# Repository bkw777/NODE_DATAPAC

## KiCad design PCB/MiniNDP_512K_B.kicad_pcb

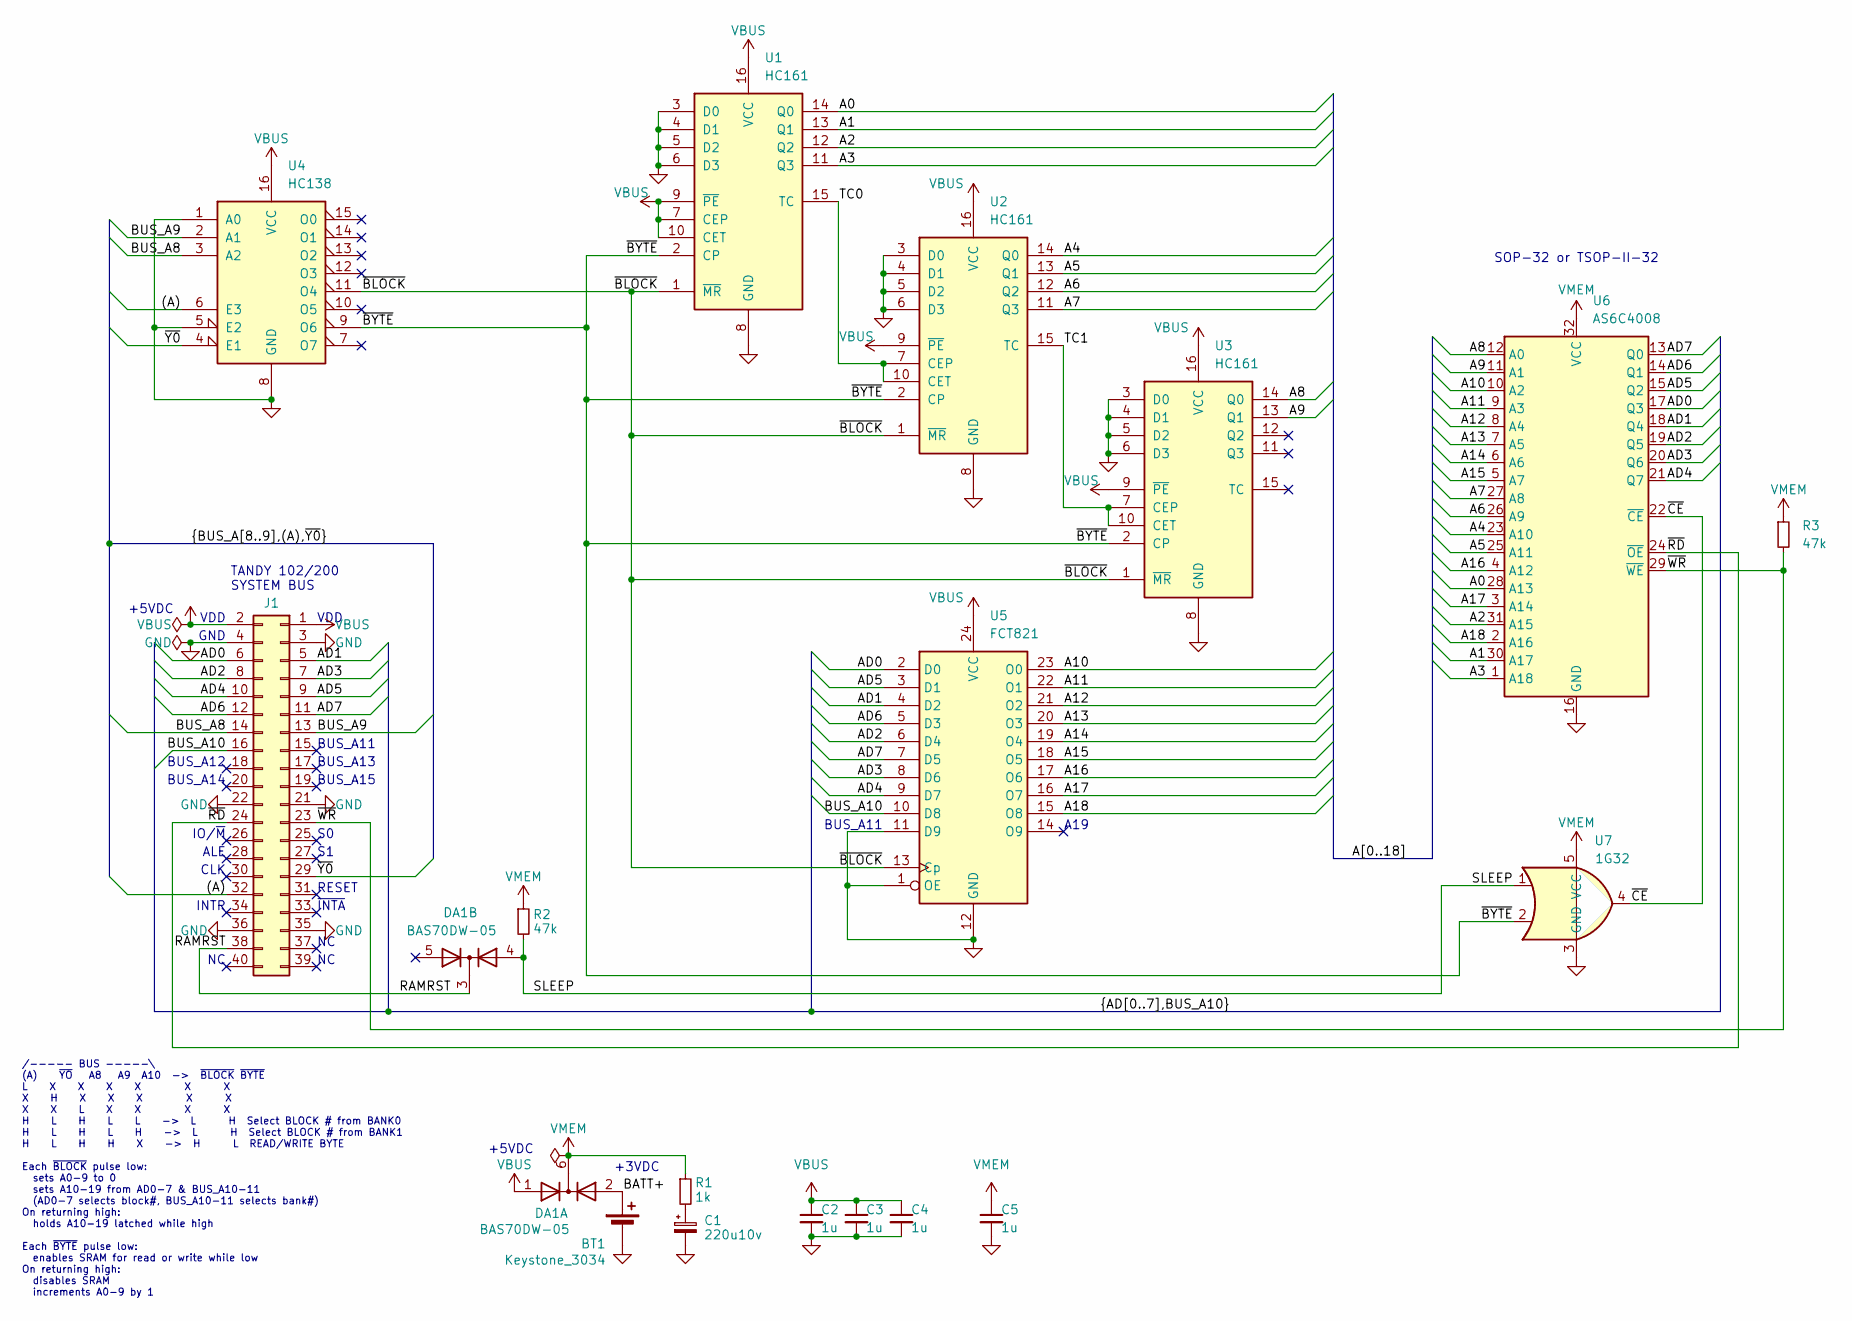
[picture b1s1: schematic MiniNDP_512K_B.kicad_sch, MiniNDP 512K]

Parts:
BT1: Keystone_3034; Keystone_3028_3034
C1: 220u10v; CP_6032
C2, C3, C4, C5: 1u; C_0805
DA1: BAS70DW-05; SOT-363_SC-70-6_symmetric
J1: Conn_02x20_Odd_Even; IDC-Header_2x20_P2.54mm_Vertical
R1: 1k; R_0805
R2, R3: 47k; R_0805
U1, U2, U3: HC161; TSSOP-16
U4: HC138; TSSOP-16
U5: FCT821; SOIC-24
U6: AS6C4008; TSOP-II-SOP-32_dual
U7: 1G32; SOT-353_SC-70-5

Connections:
/(A): J1.32, U4.6 (E3)
/A0: U1.14 (Q0), U6.28 (A13)
/A1: U1.13 (Q1), U6.30 (A17)
/A2: U1.12 (Q2), U6.31 (A15)
/A3: U1.11 (Q3), U6.1 (A18)
/A4: U2.14 (Q0), U6.23 (A10)
/A5: U2.13 (Q1), U6.25 (A11)
/A6: U2.12 (Q2), U6.26 (A9)
/A7: U2.11 (Q3), U6.27 (A8)
/A8: U3.14 (Q0), U6.12 (A0)
/A9: U3.13 (Q1), U6.11 (A1)
/A10: U5.23 (O0), U6.10 (A2)
/A11: U5.22 (O1), U6.9 (A3)
/A12: U5.21 (O2), U6.8 (A4)
/A13: U5.20 (O3), U6.7 (A5)
/A14: U5.19 (O4), U6.6 (A6)
/A15: U5.18 (O5), U6.5 (A7)
/A16: U5.17 (O6), U6.4 (A12)
/A17: U5.16 (O7), U6.3 (A14)
/A18: U5.15 (O8), U6.2 (A16)
/AD0: J1.6, U5.2 (D0), U6.17 (Q3)
/AD1: J1.5, U5.4 (D2), U6.18 (Q4)
/AD2: J1.8, U5.6 (D4), U6.19 (Q5)
/AD3: J1.7, U5.8 (D6), U6.20 (Q6)
/AD4: J1.10, U5.9 (D7), U6.21 (Q7)
/AD5: J1.9, U5.3 (D1), U6.15 (Q2)
/AD6: J1.12, U5.5 (D3), U6.14 (Q1)
/AD7: J1.11, U5.7 (D5), U6.13 (Q0)
/BATT+: BT1.1 (+), DA1.2 (A)
/BUS_A8: J1.14, U4.3 (A2)
/BUS_A9: J1.13, U4.2 (A1)
/BUS_A10: J1.16, U5.10 (D8)
/RAMRST: DA1.3 (K), J1.38
/SLEEP: DA1.4 (A), R2.2, U7.1
/TC0: U1.15 (TC), U2.7 (CEP), U2.10 (CET)
/TC1: U2.15 (TC), U3.7 (CEP), U3.10 (CET)
/~BLOCK: U1.1 (~MR), U2.1 (~MR), U3.1 (~MR), U4.11 (O4), U5.13 (Cp)
/~BYTE: U1.2 (CP), U2.2 (CP), U3.2 (CP), U4.9 (O6), U7.2
/~CE: U6.22 (~CE), U7.4
/~RD: J1.24, U6.24 (~OE)
/~WR: J1.23, R3.2, U6.29 (~WE)
/~Y0: J1.29, U4.4 (E1)
GND: BT1.2 (-), C1.2, C2.2, C3.2, C4.2, C5.2, J1.3, J1.4, J1.21, J1.22, J1.35, J1.36, U1.3 (D0), U1.4 (D1), U1.5 (D2), U1.6 (D3), U1.8 (GND), U2.3 (D0), U2.4 (D1), U2.5 (D2), U2.6 (D3), U2.8 (GND), U3.3 (D0), U3.4 (D1), U3.5 (D2), U3.6 (D3), U3.8 (GND), U4.1 (A0), U4.5 (E2), U4.8 (GND), U5.1 (OE), U5.11 (D9), U5.12 (GND), U6.16 (GND), U7.3 (GND)
unnamed: C1.1, R1.2
VBUS: C2.1, C3.1, C4.1, DA1.1 (A), J1.1, J1.2, U1.7 (CEP), U1.9 (~PE), U1.10 (CET), U1.16 (VCC), U2.9 (~PE), U2.16 (VCC), U3.9 (~PE), U3.16 (VCC), U4.16 (VCC), U5.24 (VCC)
VMEM: C5.1, DA1.6 (K), R1.1, R2.1, R3.1, U6.32 (VCC), U7.5 (VCC)

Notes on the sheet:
BUS_A11
TANDY 102/200 SYSTEM BUS
+5VDC
BUS_A15
INTR
BUS_A14
ALE
SOP-32 or TSOP-II-32
~{INTA}
CLK
GND
IO/~{M}
VDD
/----- BUS -----\ (A) ~{YO} A8 A9 A10 -> ~{BLOCK} ~{BYTE} L X X X X X X X H X X X X X X X L X X X X H L H L L -> L H Select BLOCK # from BANK0 H L H L H -> L H Select BLOCK # from BANK1 H L H H X -> H L READ/WRITE BYTE Each ~{BLOCK} pulse low: sets A0-9 to 0 sets A10-19 from AD0-7 & BUS_A10-11 (AD0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
+3VDC
RESET
A19
BUS_A13
BUS_A12

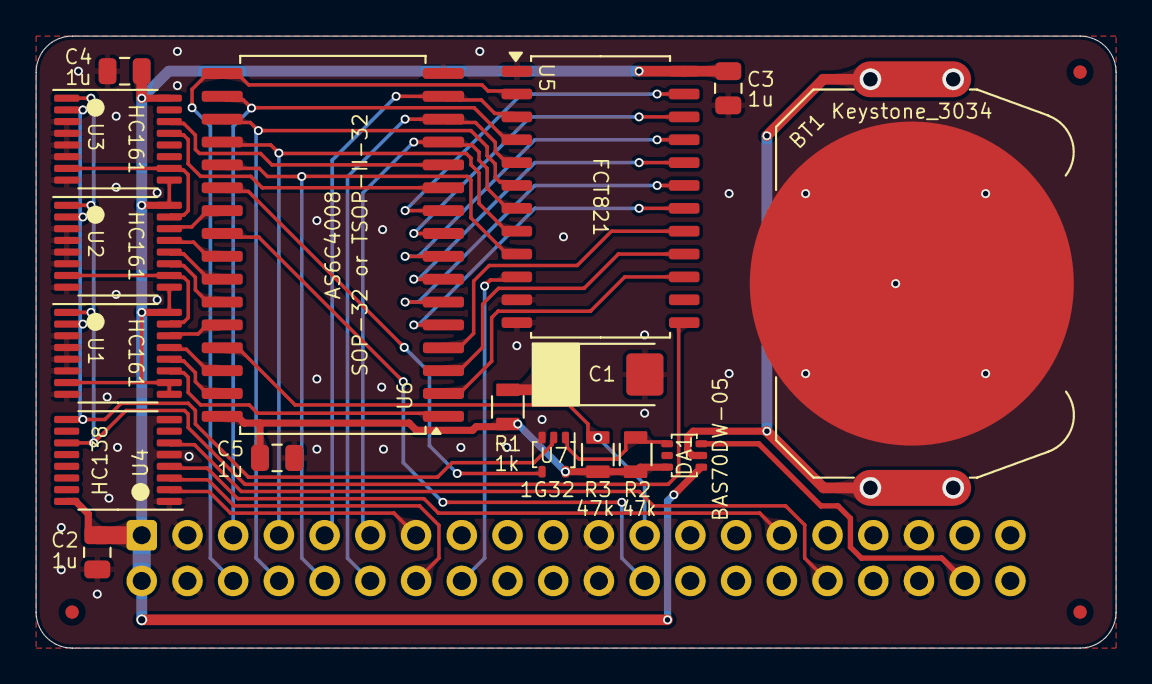
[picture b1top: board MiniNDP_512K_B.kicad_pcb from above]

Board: 2 copper layers, 60.0 x 34.0 mm, 22 parts (1 on the bottom side), 46 nets.

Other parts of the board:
ENCLOSURE: MiniNDP_Cover
F2, F2#2, F3: Fiducial_0.75_1.5

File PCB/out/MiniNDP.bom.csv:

"Reference","Value","Datasheet","Footprint","Qty","DNP","MPN","Description"
"BT1","Keystone_3034","datasheets/Keystone_3034.pdf","000_LOCAL:Keystone_3028_3034","1","","Keystone 3034","SMT 20mm x 3.2mm coin cell holder"
"C1","220u10v","datasheets/TAJ.odf","000_LOCAL:CP_6032","1","","TAJC227K010RNJ","CAP TANT 220UF 10% 10V 2312"
"C2,C3,C4,C5","1u","datasheets/CL21B105KAFNNNE.pdf","000_LOCAL:C_0805","4","","CL21B105KAFNNNE","CAP CER 1UF 25V X7R 0805"
"DA1","BAS70DW-05","datasheets/BAS70.pdf","000_LOCAL:SOT-363_SC-70-6_symmetric","1","","BAS70DW-05-7-F","DIODE ARR SCHOTT 70V 70MA SOT363 2-PAIR COMMON-CATHODE"
"J1","Conn_02x20_Odd_Even","datasheets/2x20_male_boxed.pdf","000_LOCAL:IDC-Header_2x20_P2.54mm_Vertical","1","","302-S401","CONN HEADER VERT 40POS 2.54MM"
"R1","1k","datasheets/RK73.pdf","000_LOCAL:R_0805","1","","RK73B2ATTD102J","RES 1K OHM 5% 1/4W 0805"
"R2,R3","47k","datasheets/sei-rmcf_rmcp.pdf","000_LOCAL:R_0805","2","","RMCF0805FT47K0","RES 47K OHM 1% 1/8W 0805"
"U1,U2,U3","HC161","datasheets/HC161.pdf","000_LOCAL:TSSOP-16","3","","74HC161PW,118","IC BINARY COUNTER 4-BIT 16TSSOP"
"U4","HC138","datasheets/HC138.pdf","000_LOCAL:TSSOP-16","1","","74HC138PW,118","IC DECODER/DEMUX 1X3:8 16TSSOP"
"U5","HC574","datasheets/HC574.pdf","000_LOCAL:TSSOP-20","1","","74HC574PW,118","IC FF D-TYPE SNGL 8BIT 20TSSOP"
"U6","AS6C4008","datasheets/AS6C4008.pdf","000_LOCAL:TSOP32-dual","1","","AS6C4008-55STIN","IC SRAM 512Kx8 PARALLEL STSOP-32"
"U7","1G32","datasheets/LVC1G32.pdf","000_LOCAL:SOT-353_SC-70-5","1","","74LVC1G32GW,125","IC GATE OR 1CH 2-INP 5TSSOP"
"U8","1G79","datasheets/LVC1G79.pdf","000_LOCAL:SOT-353_SC-70-5","1","","74LVC1G79GW,125","IC FF D-TYPE SNGL 1BIT 5TSSOP"

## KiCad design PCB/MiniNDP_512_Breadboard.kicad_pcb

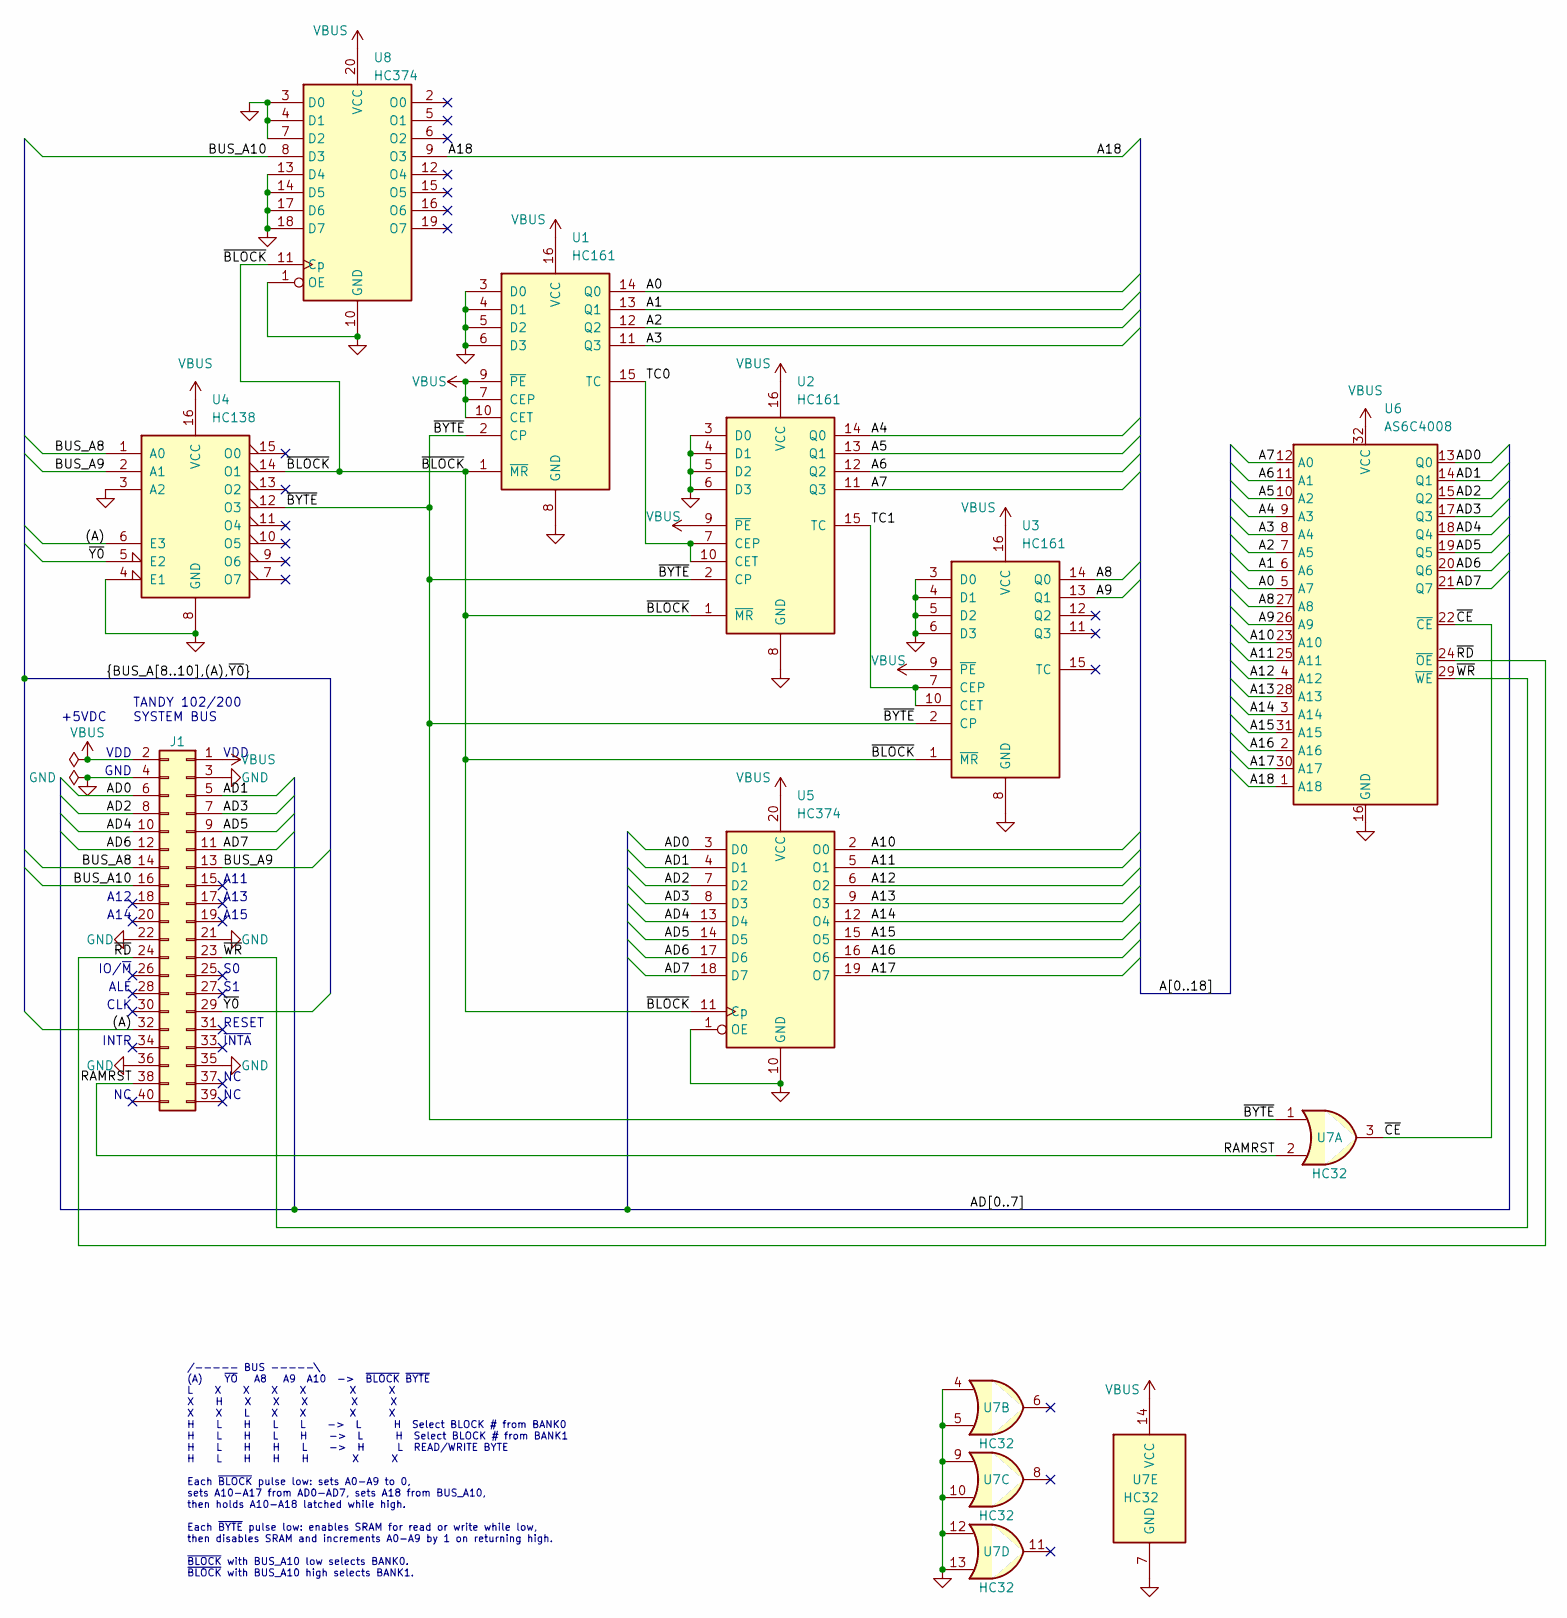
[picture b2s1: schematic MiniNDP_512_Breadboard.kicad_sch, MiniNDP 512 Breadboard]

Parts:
J1: Conn_02x20_Odd_Even; IDC-Header_2x20_P2.54mm_Vertical
U1, U2, U3: HC161; DIP-16_W7.62mm
U4: HC138; DIP-16_W7.62mm
U5, U8: HC374; DIP-20_W7.62mm
U6: AS6C4008; DIP-32_W15.24mm
U7: HC32; DIP-14_W7.62mm

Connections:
/(A): J1.32, U4.6 (E3)
/A0: U1.14 (Q0), U6.5 (A7)
/A1: U1.13 (Q1), U6.6 (A6)
/A2: U1.12 (Q2), U6.7 (A5)
/A3: U1.11 (Q3), U6.8 (A4)
/A4: U2.14 (Q0), U6.9 (A3)
/A5: U2.13 (Q1), U6.10 (A2)
/A6: U2.12 (Q2), U6.11 (A1)
/A7: U2.11 (Q3), U6.12 (A0)
/A8: U3.14 (Q0), U6.27 (A8)
/A9: U3.13 (Q1), U6.26 (A9)
/A10: U5.2 (O0), U6.23 (A10)
/A11: U5.5 (O1), U6.25 (A11)
/A12: U5.6 (O2), U6.4 (A12)
/A13: U5.9 (O3), U6.28 (A13)
/A14: U5.12 (O4), U6.3 (A14)
/A15: U5.15 (O5), U6.31 (A15)
/A16: U5.16 (O6), U6.2 (A16)
/A17: U5.19 (O7), U6.30 (A17)
/A18: U6.1 (A18), U8.9 (O3)
/AD0: J1.6, U5.3 (D0), U6.13 (Q0)
/AD1: J1.5, U5.4 (D1), U6.14 (Q1)
/AD2: J1.8, U5.7 (D2), U6.15 (Q2)
/AD3: J1.7, U5.8 (D3), U6.17 (Q3)
/AD4: J1.10, U5.13 (D4), U6.18 (Q4)
/AD5: J1.9, U5.14 (D5), U6.19 (Q5)
/AD6: J1.12, U5.17 (D6), U6.20 (Q6)
/AD7: J1.11, U5.18 (D7), U6.21 (Q7)
/BUS_A8: J1.14, U4.1 (A0)
/BUS_A9: J1.13, U4.2 (A1)
/BUS_A10: J1.16, U8.8 (D3)
/RAMRST: J1.38, U7.2
/TC0: U1.15 (TC), U2.7 (CEP), U2.10 (CET)
/TC1: U2.15 (TC), U3.7 (CEP), U3.10 (CET)
/~BLOCK: U1.1 (~MR), U2.1 (~MR), U3.1 (~MR), U4.14 (O1), U5.11 (Cp), U8.11 (Cp)
/~BYTE: U1.2 (CP), U2.2 (CP), U3.2 (CP), U4.12 (O3), U7.1
/~CE: U6.22 (~CE), U7.3
/~RD: J1.24, U6.24 (~OE)
/~WR: J1.23, U6.29 (~WE)
/~Y0: J1.29, U4.5 (E2)
GND: J1.3, J1.4, J1.21, J1.22, J1.35, J1.36, U1.3 (D0), U1.4 (D1), U1.5 (D2), U1.6 (D3), U1.8 (GND), U2.3 (D0), U2.4 (D1), U2.5 (D2), U2.6 (D3), U2.8 (GND), U3.3 (D0), U3.4 (D1), U3.5 (D2), U3.6 (D3), U3.8 (GND), U4.3 (A2), U4.4 (E1), U4.8 (GND), U5.1 (OE), U5.10 (GND), U6.16 (GND), U7.4, U7.5, U7.7 (GND), U7.9, U7.10, U7.12, U7.13, U8.1 (OE), U8.3 (D0), U8.4 (D1), U8.7 (D2), U8.10 (GND), U8.13 (D4), U8.14 (D5), U8.17 (D6), U8.18 (D7)
VBUS: J1.1, J1.2, U1.7 (CEP), U1.9 (~PE), U1.10 (CET), U1.16 (VCC), U2.9 (~PE), U2.16 (VCC), U3.9 (~PE), U3.16 (VCC), U4.16 (VCC), U5.20 (VCC), U6.32 (VCC), U7.14 (VCC), U8.20 (VCC)

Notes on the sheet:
TANDY 102/200 SYSTEM BUS
+5VDC
A15
INTR
A14
ALE
~{INTA}
CLK
GND
/----- BUS -----\ (A) ~{YO} A8 A9 A10 -> ~{BLOCK} ~{BYTE} L X X X X X X X H X X X X X X X L X X X X H L H L L -> L H Select BLOCK # from BANK0 H L H L H -> L H Select BLOCK # from BANK1 H L H H L -> H L READ/WRITE BYTE H L H H H X X Each ~{BLOCK} pulse low: sets A0-A9 to 0, sets A10-A17 from AD0-AD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
IO/~{M}
VDD
RESET
A11
A13
A12

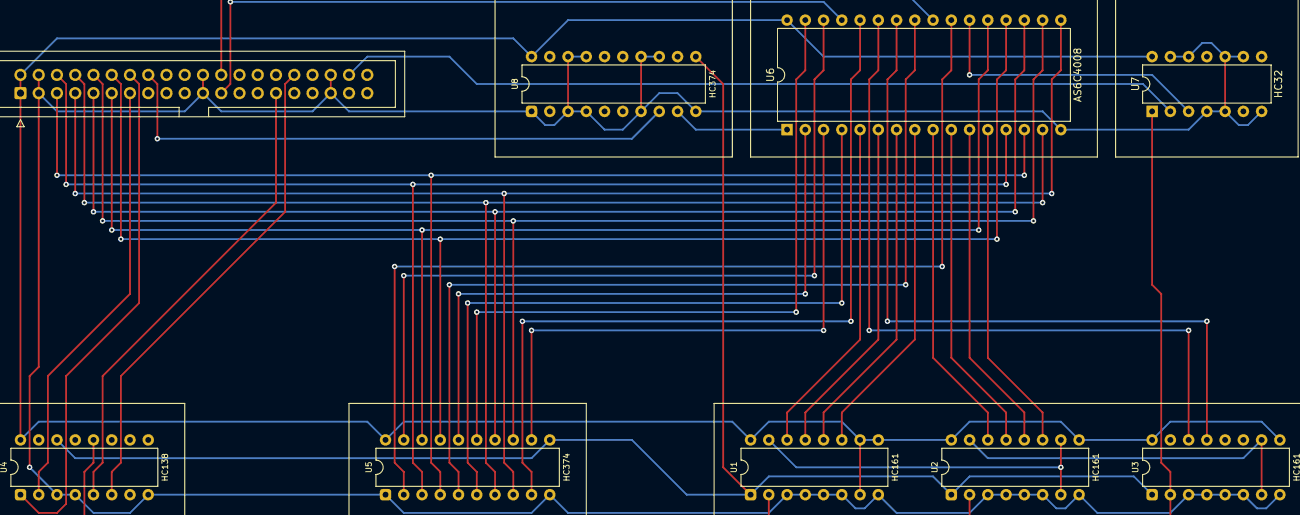
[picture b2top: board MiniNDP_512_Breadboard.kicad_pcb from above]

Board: 2 copper layers, 9 parts (0 on the bottom side), 42 nets.

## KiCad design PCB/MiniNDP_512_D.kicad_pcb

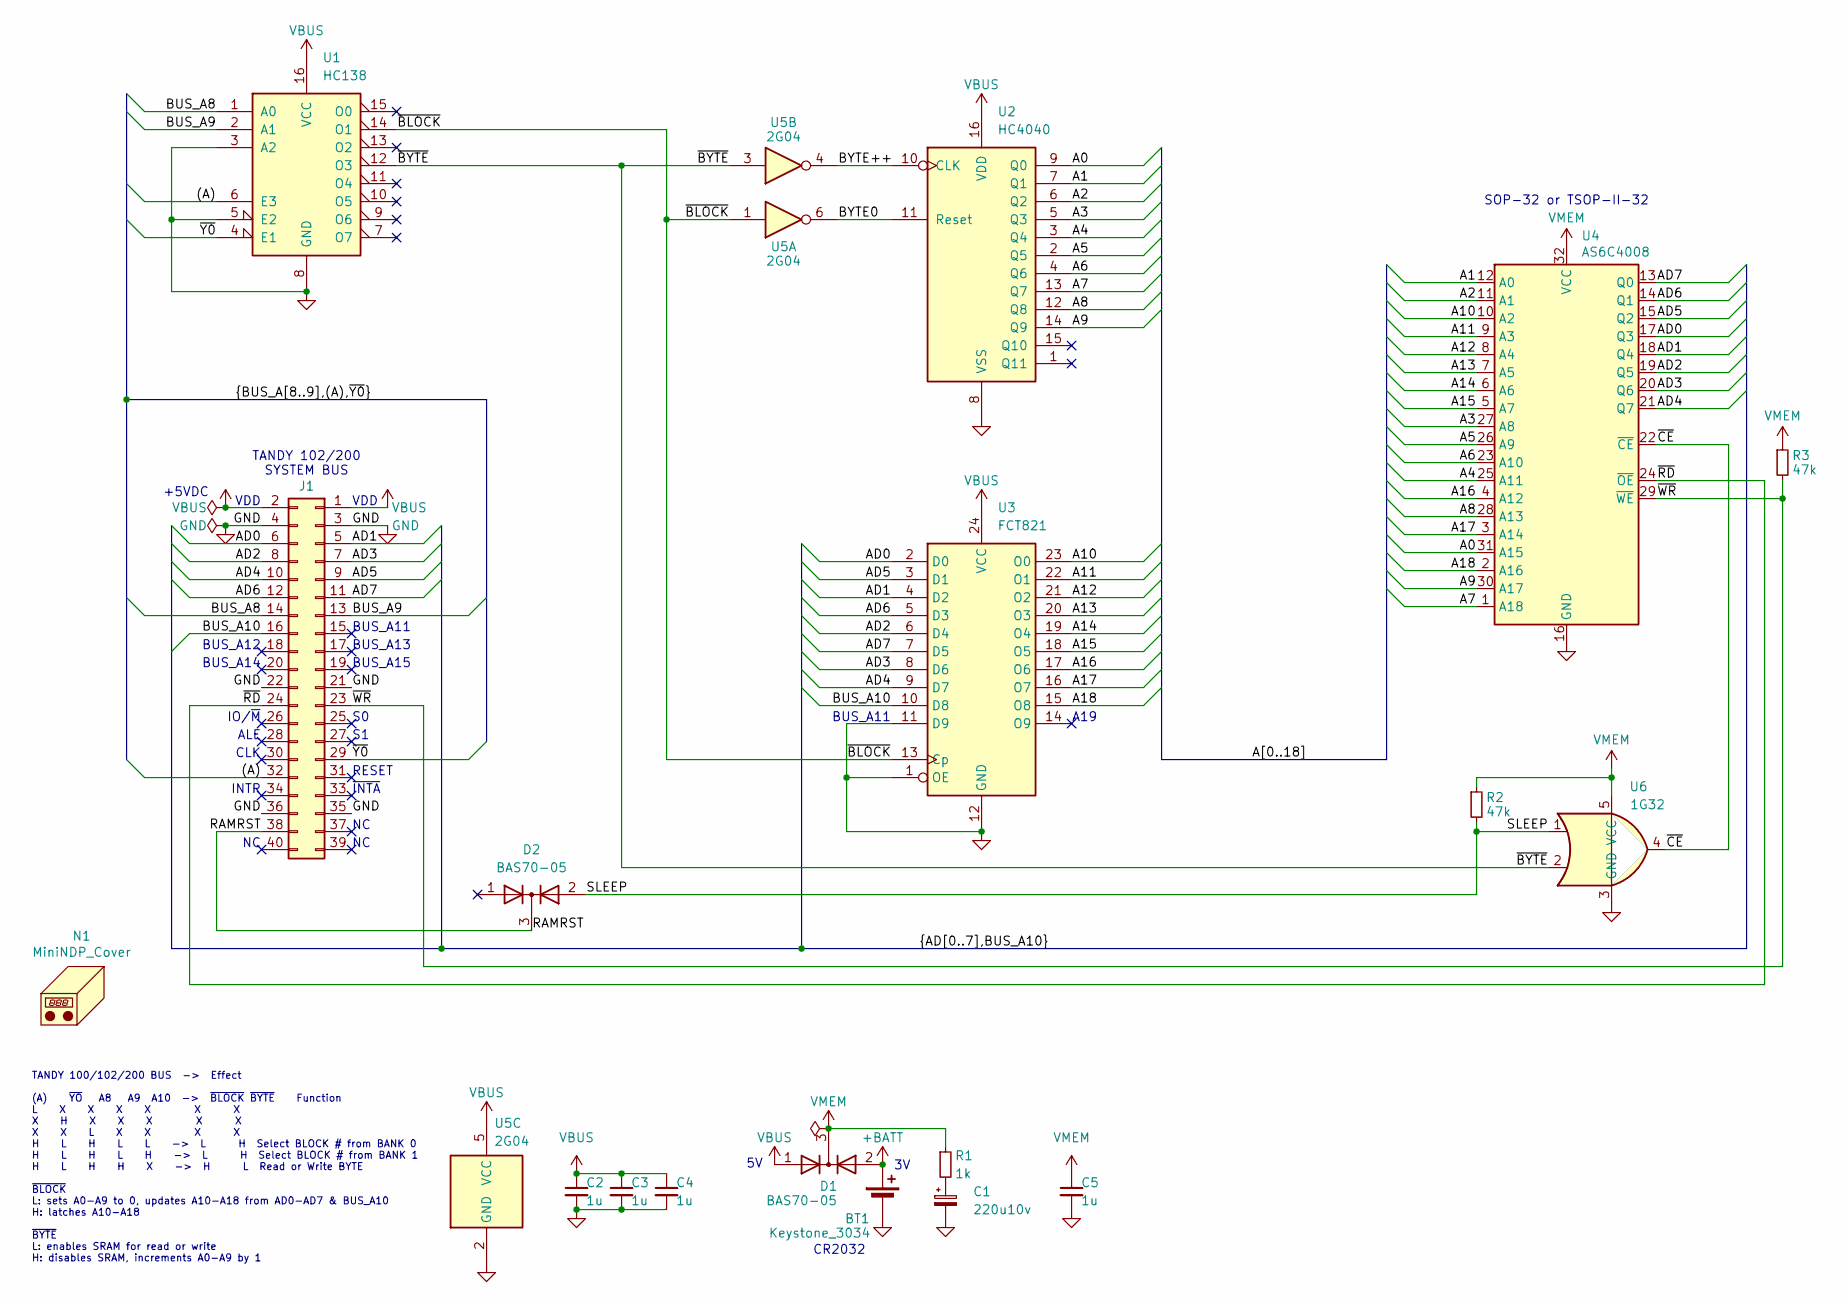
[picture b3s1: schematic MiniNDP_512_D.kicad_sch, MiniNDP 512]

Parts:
BT1: Keystone_3034; Keystone_3028_3034; MPN Keystone 3034
C1: 220u10v; CP_6032; MPN TAJC227K010RNJ
C2, C3, C4, C5: 1u; C_0805; MPN CL21B105KAFNNNE
D1, D2: BAS70-05; SOT-23; MPN BAS70-05-E3-08
J1: Conn_02x20_Odd_Even; IDC-Header_2x20_P2.54mm_Vertical; MPN 302-S401
N1: MiniNDP_Cover; MPN MiniNDP_Cover.stl
R1: 1k; R_0805; MPN RK73B2ATTD102J
R2, R3: 47k; R_0805; MPN RMCF0805FT47K0
U1: HC138; SOIC-16_3.9x9.9mm_P1.27mm; MPN 74AHC138D,118
U2: HC4040; SOIC-16_3.9x9.9mm_P1.27mm; MPN IC BINARY COUNTER 12-BIT 16SO
U3: FCT821; SOIC-24; MPN CY74FCT821BTSOC
U4: AS6C4008; TSOP-II-SOP-32_dual; MPN AS6C4008-55ZIN
U5: 2G04; TSOP-6_1.65x3.05mm_P0.95mm; MPN 74HC2G04GW,125
U6: 1G32; SOT-23-5; MPN SN74AHC1G32DBVR

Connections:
+BATT: BT1.1 (+), D1.2 (A)
/(A): J1.32, U1.6 (E3)
/A0: U2.9 (Q0), U4.31 (A15)
/A1: U2.7 (Q1), U4.12 (A0)
/A2: U2.6 (Q2), U4.11 (A1)
/A3: U2.5 (Q3), U4.27 (A8)
/A4: U2.3 (Q4), U4.25 (A11)
/A5: U2.2 (Q5), U4.26 (A9)
/A6: U2.4 (Q6), U4.23 (A10)
/A7: U2.13 (Q7), U4.1 (A18)
/A8: U2.12 (Q8), U4.28 (A13)
/A9: U2.14 (Q9), U4.30 (A17)
/A10: U3.23 (O0), U4.10 (A2)
/A11: U3.22 (O1), U4.9 (A3)
/A12: U3.21 (O2), U4.8 (A4)
/A13: U3.20 (O3), U4.7 (A5)
/A14: U3.19 (O4), U4.6 (A6)
/A15: U3.18 (O5), U4.5 (A7)
/A16: U3.17 (O6), U4.4 (A12)
/A17: U3.16 (O7), U4.3 (A14)
/A18: U3.15 (O8), U4.2 (A16)
/AD0: J1.6, U3.2 (D0), U4.17 (Q3)
/AD1: J1.5, U3.4 (D2), U4.18 (Q4)
/AD2: J1.8, U3.6 (D4), U4.19 (Q5)
/AD3: J1.7, U3.8 (D6), U4.20 (Q6)
/AD4: J1.10, U3.9 (D7), U4.21 (Q7)
/AD5: J1.9, U3.3 (D1), U4.15 (Q2)
/AD6: J1.12, U3.5 (D3), U4.14 (Q1)
/AD7: J1.11, U3.7 (D5), U4.13 (Q0)
/BUS_A8: J1.14, U1.1 (A0)
/BUS_A9: J1.13, U1.2 (A1)
/BUS_A10: J1.16, U3.10 (D8)
/BYTE0: U2.11 (Reset), U5.6
/BYTE++: U2.10 (CLK), U5.4
/RAMRST: D2.3 (K), J1.38
/SLEEP: D2.2 (A), R2.2, U6.1
/~BLOCK: U1.14 (O1), U3.13 (Cp), U5.1
/~BYTE: U1.12 (O3), U5.3, U6.2
/~CE: U4.22 (~CE), U6.4
/~RD: J1.24, U4.24 (~OE)
/~WR: J1.23, R3.2, U4.29 (~WE)
/~Y0: J1.29, U1.4 (E1)
GND: BT1.2 (-), C1.2, C2.2, C3.2, C4.2, C5.2, J1.3, J1.4, J1.21, J1.22, J1.35, J1.36, U1.3 (A2), U1.5 (E2), U1.8 (GND), U2.8 (VSS), U3.1 (OE), U3.11 (D9), U3.12 (GND), U4.16 (GND), U5.2 (GND), U6.3 (GND)
unnamed: C1.1, R1.2
VBUS: C2.1, C3.1, C4.1, D1.1 (A), J1.1, J1.2, U1.16 (VCC), U2.16 (VDD), U3.24 (VCC), U5.5 (VCC)
VMEM: C5.1, D1.3 (K), R1.1, R2.1, R3.1, U4.32 (VCC), U6.5 (VCC)

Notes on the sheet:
BUS_A11
TANDY 102/200 SYSTEM BUS
+5VDC
BUS_A15
INTR
BUS_A14
ALE
SOP-32 or TSOP-II-32
~{INTA}
CR2032
CLK
IO/~{M}
VDD
RESET
A19
BUS_A13
TANDY 100/102/200 BUS -> Effect (A) ~{YO} A8 A9 A10 -> ~{BLOCK} ~{BYTE} Function L X X X X X X X H X X X X X X X L X X X X H L H L L -> L H Select BLOCK # from BANK 0 H L H L H -> L H Select BLOCK # from BANK 1 H L H H X -> H L Read or Write BYTE ~{BLOCK} L: sets A0-A9 to 0, updates A10-A18 from AD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
BUS_A12

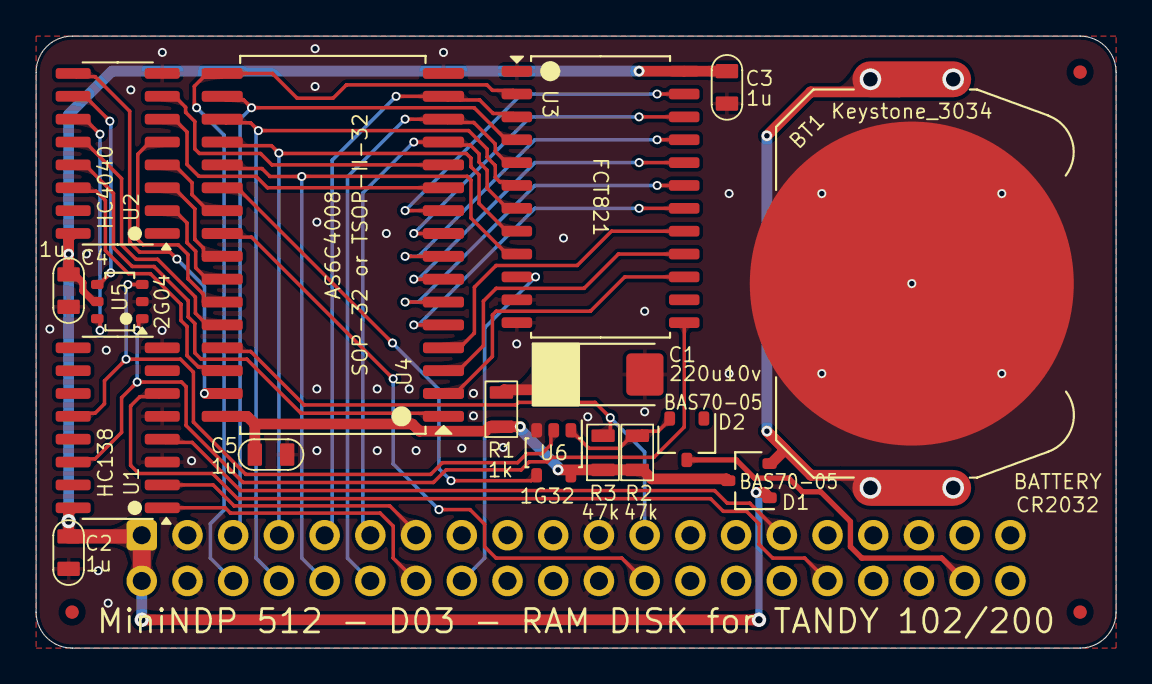
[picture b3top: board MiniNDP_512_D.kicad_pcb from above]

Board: 2 copper layers, 60.0 x 34.0 mm, 22 parts (1 on the bottom side), 46 nets.

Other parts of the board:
F2, F2#2, F3: Fiducial_0.75_1.5

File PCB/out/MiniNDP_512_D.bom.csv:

"Reference","Value","Datasheet","Footprint","Qty","DNP","MPN","Description"
"BT1","Keystone_3034","datasheets/Keystone_3034.pdf","000_LOCAL:Keystone_3028_3034","1","","Keystone 3034","SMT 20mm x 3.2mm coin cell holder"
"C1","220u10v","datasheets/TAJ.odf","000_LOCAL:CP_6032","1","","TAJC227K010RNJ","CAP TANT 220UF 10% 10V 2312"
"C2,C3,C4,C5","1u","datasheets/CL21B105KAFNNNE.pdf","000_LOCAL:C_0805","4","","CL21B105KAFNNNE","CAP CER 1UF 25V X7R 0805"
"D1,D2","BAS70-05","datasheets/BAS70-00_to_BAS70-06.pdf","000_LOCAL:SOT-23","2","","BAS70-05-E3-08","DIODE ARR SCHOTT 70V 200MA SOT23"
"J1","Conn_02x20_Odd_Even","datasheets/2x20_male_boxed.pdf","000_LOCAL:IDC-Header_2x20_P2.54mm_Vertical","1","","302-S401","CONN HEADER VERT 40POS 2.54MM"
"R1","1k","datasheets/RK73.pdf","000_LOCAL:R_0805","1","","RK73B2ATTD102J","RES 1K OHM 5% 1/4W 0805"
"R2,R3","47k","datasheets/sei-rmcf_rmcp.pdf","000_LOCAL:R_0805","2","","RMCF0805FT47K0","RES 47K OHM 1% 1/8W 0805"
"U1","HC138","datasheets/74xx138.pdf","000_LOCAL:SOIC-16_3.9x9.9mm_P1.27mm","1","","74AHC138D,118","IC DECODER/DEMUX 1 X 3:8 16SO"
"U2","HC4040","datasheets/4040.pdf","000_LOCAL:SOIC-16_3.9x9.9mm_P1.27mm","1","","IC BINARY COUNTER 12-BIT 16SO","74HC4040D,653"
"U3","FCT821","datasheets/CY74FCT821T.pdf","000_LOCAL:SOIC-24","1","","CY74FCT821BTSOC","IC FF D-TYPE SNGL 10BIT 24SOIC"
"U4","AS6C4008","datasheets/AS6C4008.pdf","000_LOCAL:TSOP-II-SOP-32_dual","1","","AS6C4008-55ZIN","IC SRAM 512Kx8 PARALLEL 5v TSOP-II-32"
"U5","2G04","datasheets/2G04.pdf","000_LOCAL:TSOP-6_1.65x3.05mm_P0.95mm","1","","74HC2G04GW,125","IC INVERTER 2CH 2-INP 6TSSOP"
"U6","1G32","datasheets/74xx1G32.pdf","000_LOCAL:SOT-23-5","1","","SN74AHC1G32DBVR","IC GATE OR 1CH 2-INP SOT23-5"

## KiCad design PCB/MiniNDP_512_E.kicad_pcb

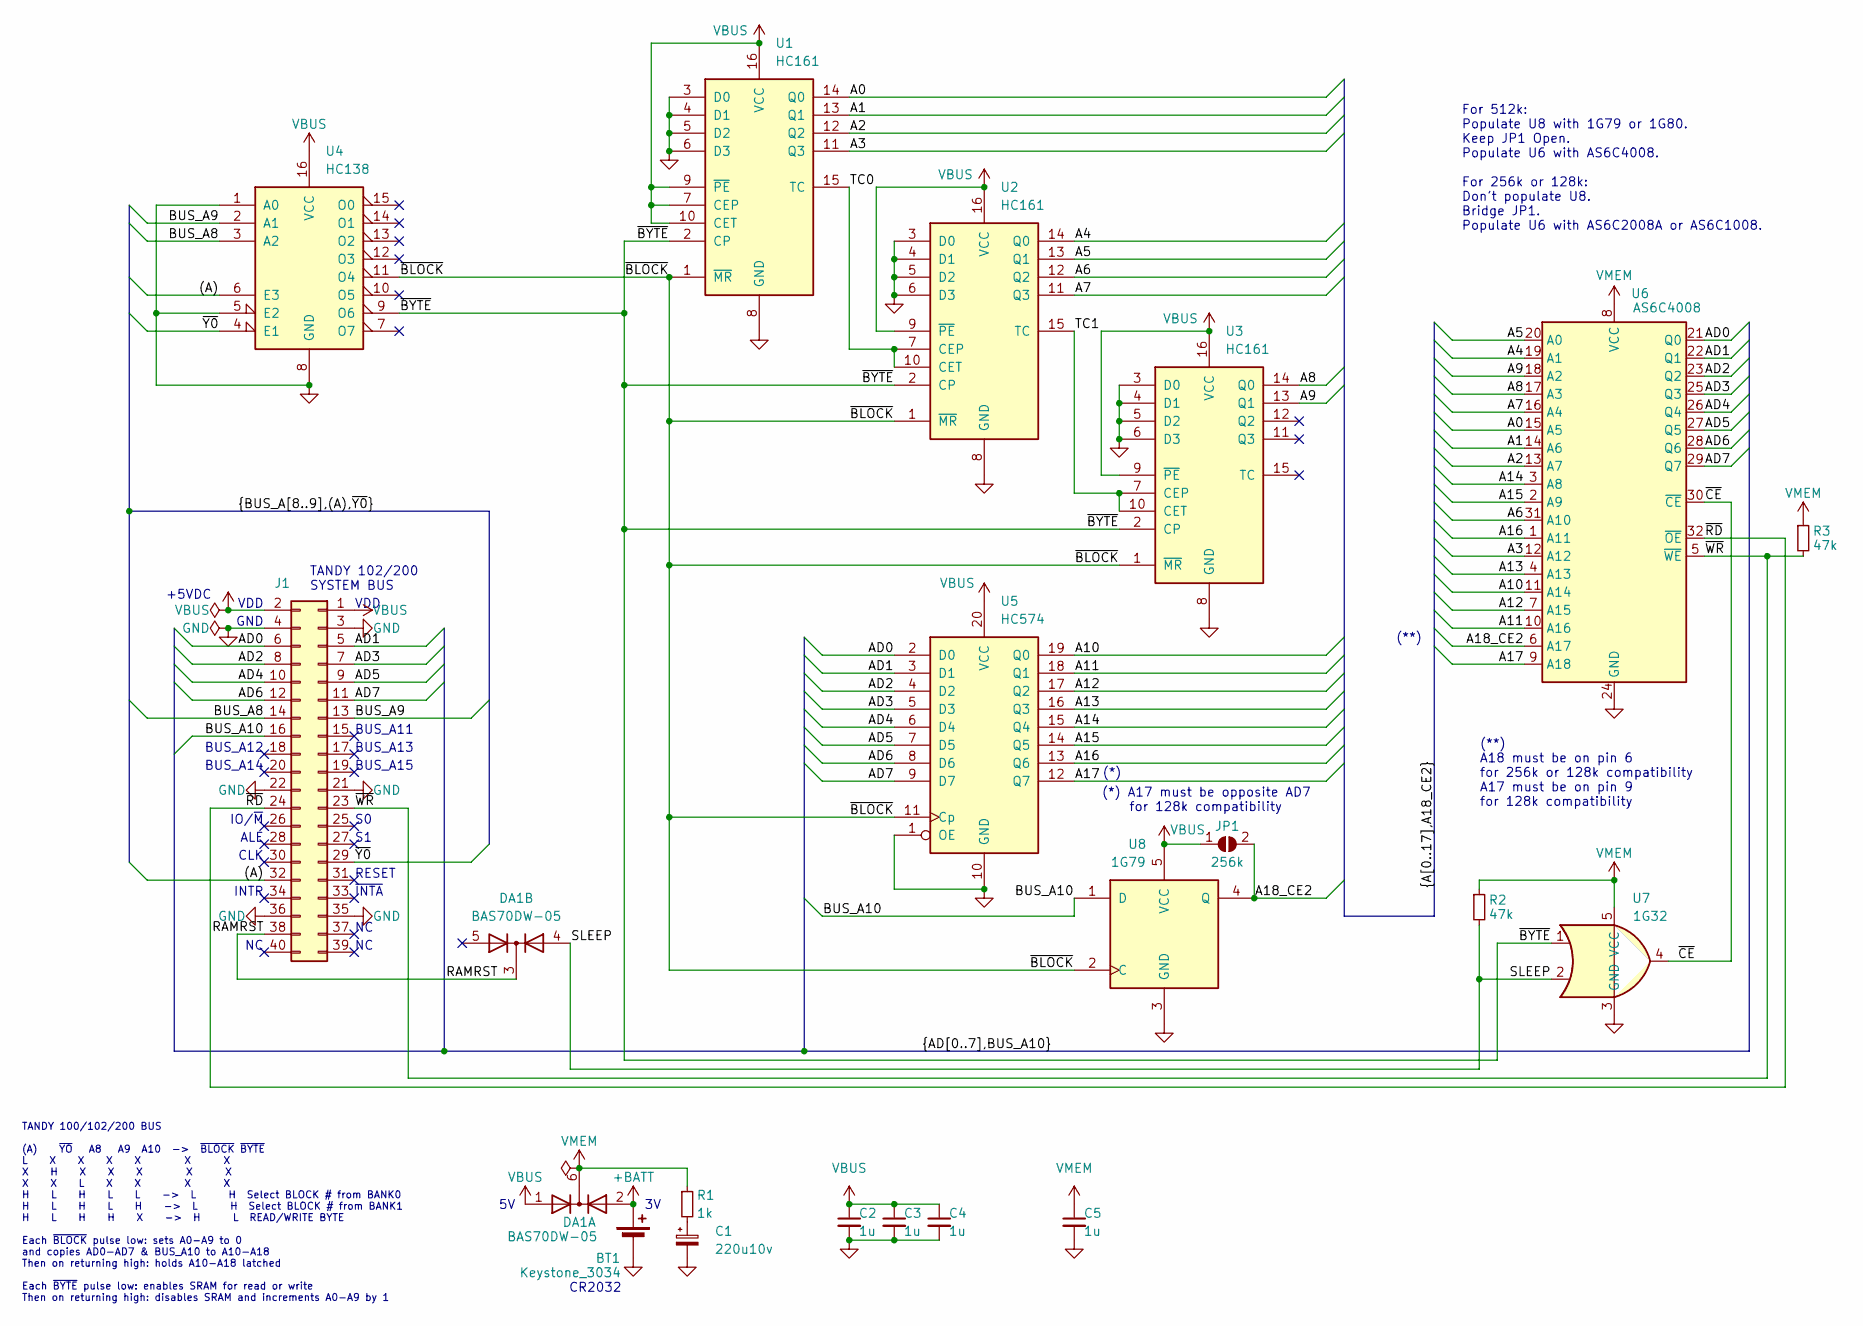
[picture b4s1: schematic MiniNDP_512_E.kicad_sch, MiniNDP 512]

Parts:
BT1: Keystone_3034; Keystone_3028_3034; MPN Keystone 3034
C1: 220u10v; CP_6032; MPN TAJC227K010RNJ
C2, C3, C4, C5: 1u; C_0805; MPN CL21B105KAFNNNE
DA1: BAS70DW-05; SOT-363_SC-70-6_symmetric; MPN BAS70DW-05-7-F
J1: Conn_02x20_Odd_Even; IDC-Header_2x20_P2.54mm_Vertical; MPN 302-S401
JP1: 256k; SolderJumper-2_Open 0.65mm
R1: 1k; R_0805; MPN RK73B2ATTD102J
R2, R3: 47k; R_0805; MPN RMCF0805FT47K0
U1, U2, U3: HC161; TSSOP-16; MPN 74HC161PW,118
U4: HC138; TSSOP-16; MPN 74HC138PW,118
U5: HC574; TSSOP-20; MPN 74HC574PW,118
U6: AS6C4008; TSOP32-dual; MPN AS6C4008-55STIN
U7: 1G32; SOT-353_SC-70-5; MPN 74LVC1G32GW,125
U8: 1G79; SOT-353_SC-70-5; MPN 74LVC1G79GW,125

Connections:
+BATT: BT1.1 (+), DA1.2 (A)
/(A): J1.32, U4.6 (E3)
/A0: U1.14 (Q0), U6.15 (A5)
/A1: U1.13 (Q1), U6.14 (A6)
/A2: U1.12 (Q2), U6.13 (A7)
/A3: U1.11 (Q3), U6.12 (A12)
/A4: U2.14 (Q0), U6.19 (A1)
/A5: U2.13 (Q1), U6.20 (A0)
/A6: U2.12 (Q2), U6.31 (A10)
/A7: U2.11 (Q3), U6.16 (A4)
/A8: U3.14 (Q0), U6.17 (A3)
/A9: U3.13 (Q1), U6.18 (A2)
/A10: U5.19 (Q0), U6.11 (A14)
/A11: U5.18 (Q1), U6.10 (A16)
/A12: U5.17 (Q2), U6.7 (A15)
/A13: U5.16 (Q3), U6.4 (A13)
/A14: U5.15 (Q4), U6.3 (A8)
/A15: U5.14 (Q5), U6.2 (A9)
/A16: U5.13 (Q6), U6.1 (A11)
/A17: U5.12 (Q7), U6.9 (A18)
/A18_CE2: JP1.2 (B), U6.6 (A17), U8.4 (Q)
/AD0: J1.6, U5.2 (D0), U6.21 (Q0)
/AD1: J1.5, U5.3 (D1), U6.22 (Q1)
/AD2: J1.8, U5.4 (D2), U6.23 (Q2)
/AD3: J1.7, U5.5 (D3), U6.25 (Q3)
/AD4: J1.10, U5.6 (D4), U6.26 (Q4)
/AD5: J1.9, U5.7 (D5), U6.27 (Q5)
/AD6: J1.12, U5.8 (D6), U6.28 (Q6)
/AD7: J1.11, U5.9 (D7), U6.29 (Q7)
/BUS_A8: J1.14, U4.3 (A2)
/BUS_A9: J1.13, U4.2 (A1)
/BUS_A10: J1.16, U8.1 (D)
/RAMRST: DA1.3 (K), J1.38
/SLEEP: DA1.4 (A), R2.2, U7.2
/TC0: U1.15 (TC), U2.7 (CEP), U2.10 (CET)
/TC1: U2.15 (TC), U3.7 (CEP), U3.10 (CET)
/~BLOCK: U1.1 (~MR), U2.1 (~MR), U3.1 (~MR), U4.11 (O4), U5.11 (Cp), U8.2 (C)
/~BYTE: U1.2 (CP), U2.2 (CP), U3.2 (CP), U4.9 (O6), U7.1
/~CE: U6.30 (~CE), U7.4
/~RD: J1.24, U6.32 (~OE)
/~WR: J1.23, R3.2, U6.5 (~WE)
/~Y0: J1.29, U4.4 (E1)
GND: BT1.2 (-), C1.2, C2.2, C3.2, C4.2, C5.2, J1.3, J1.4, J1.21, J1.22, J1.35, J1.36, U1.3 (D0), U1.4 (D1), U1.5 (D2), U1.6 (D3), U1.8 (GND), U2.3 (D0), U2.4 (D1), U2.5 (D2), U2.6 (D3), U2.8 (GND), U3.3 (D0), U3.4 (D1), U3.5 (D2), U3.6 (D3), U3.8 (GND), U4.1 (A0), U4.5 (E2), U4.8 (GND), U5.1 (OE), U5.10 (GND), U6.24 (GND), U7.3 (GND), U8.3 (GND)
unnamed: C1.1, R1.2

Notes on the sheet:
TANDY 102/200 SYSTEM BUS
+5VDC
BUS_A15
INTR
BUS_A14
ALE
~{INTA}
CLK
(**) A18 must be on pin 6 for 256k or 128k compatibility A17 must be on pin 9 for 128k compatibility
GND
For 512k: Populate U8 with 1G79 or 1G80. Keep JP1 Open. Populate U6 with AS6C4008. For 256k or 128k: Don't populate U8. Bridge JP1. Populate U6 with AS6C2008A or AS6C1008.
IO/~{M}
CR2032
VDD
TANDY 100/102/200 BUS (A) ~{YO} A8 A9 A10 -> ~{BLOCK} ~{BYTE} L X X X X X X X H X X X X X X X L X X X X H L H L L -> L H Select BLOCK # from BANK0 H L H L H -> L H Select BLOCK # from BANK1 H L H H X -> H L READ/WRITE BYTE Each ~{BLOCK} pulse low: sets A0-A9 to 0 and copies AD0-AD7 & BUS_A10 to A10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
RESET
(*) A17 must be opposite AD7 for 128k compatibility
(**)
BUS_A11
BUS_A13
(*)
BUS_A12

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
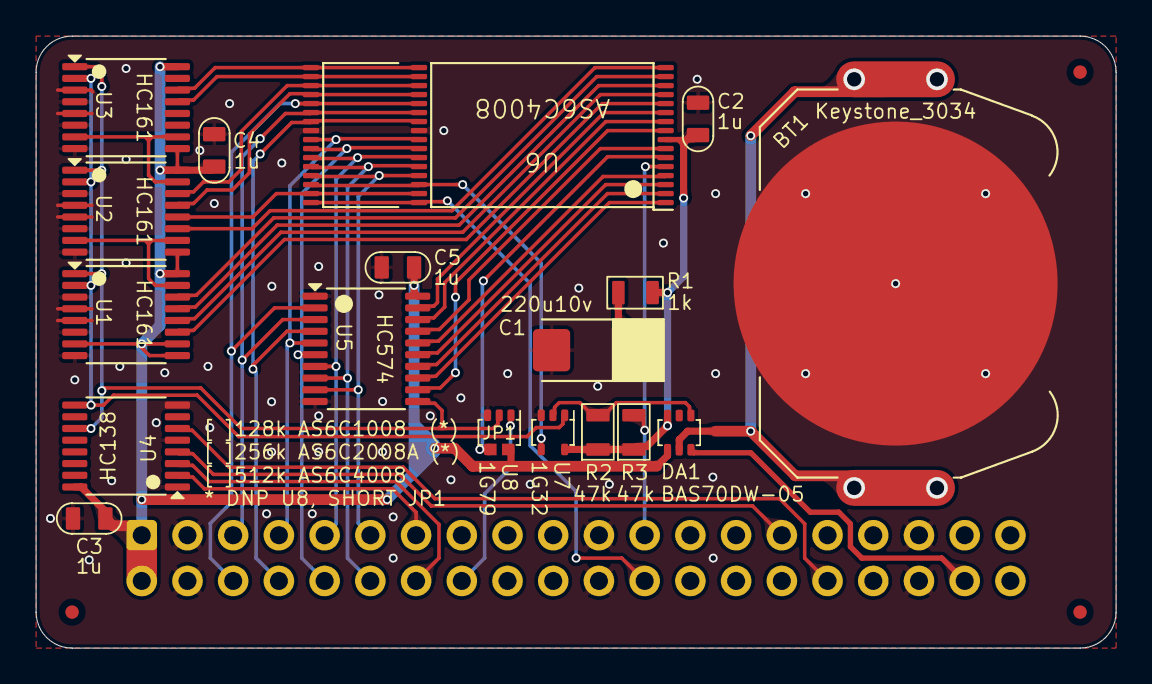
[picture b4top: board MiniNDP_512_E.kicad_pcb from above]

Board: 2 copper layers, 60.0 x 34.0 mm, 24 parts (1 on the bottom side), 46 nets.

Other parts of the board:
ENCLOSURE: MiniNDP_Cover
F3, F3#2, F3#3: Fiducial_0.75_1.5

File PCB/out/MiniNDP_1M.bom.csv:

"Reference","Value","Datasheet","Footprint","Qty","DNP","MPN","Description"
"BT1","Keystone_3034","datasheets/Keystone_3034.pdf","000_LOCAL:Keystone_3028_3034","1","","Keystone 3034","SMT 20mm x 3.2mm coin cell holder"
"C1","220u10v","datasheets/TAJ.odf","000_LOCAL:CP_6032","1","","TAJC227K010RNJ","CAP TANT 220UF 10% 10V 2312"
"C2,C3,C4,C5","1u","datasheets/CL21B105KAFNNNE.pdf","000_LOCAL:C_0805","4","","CL21B105KAFNNNE","CAP CER 1UF 25V X7R 0805"
"DA1","BAS70DW-05","datasheets/BAS70.pdf","000_LOCAL:SOT-363_SC-70-6_symmetric","1","","BAS70DW-05-7-F","DIODE ARR SCHOTT 70V 70MA SOT363 2-PAIR COMMON-CATHODE"
"J1","Conn_02x20_Odd_Even","datasheets/2x20_male_boxed.pdf","000_LOCAL:IDC-Header_2x20_P2.54mm_Vertical","1","","302-S401","CONN HEADER VERT 40POS 2.54MM"
"R1","1k","datasheets/RK73.pdf","000_LOCAL:R_0805","1","","RK73B2ATTD102J","RES 1K OHM 5% 1/4W 0805"
"R2,R3","47k","datasheets/sei-rmcf_rmcp.pdf","000_LOCAL:R_0805","2","","RMCF0805FT47K0","RES 47K OHM 1% 1/8W 0805"
"U1,U2,U3","HC161","datasheets/HC161.pdf","000_LOCAL:TSSOP-16","3","","74HC161PW,118","IC BINARY COUNTER 4-BIT 16TSSOP"
"U4","HC138","datasheets/HC138.pdf","000_LOCAL:TSSOP-16","1","","74HC138PW,118","IC DECODER/DEMUX 1X3:8 16TSSOP"
"U5","FCT821","datasheets/CY74FCT821T.pdf","000_LOCAL:SOIC-24","1","","CY74FCT821BTSOC","IC FF D-TYPE SNGL 10BIT 24SOIC"
"U6","AS6C8008_TSOPII","datasheets/AS6C8008.pdf","000_LOCAL:TSOP-II-44","1","","AS6C8008-55ZIN","IC SRAM 1Mx8 PARALLEL 5v TSOP-II-44"
"U7","1G32","datasheets/LVC1G32.pdf","000_LOCAL:SOT-353_SC-70-5","1","","74LVC1G32GW,125","IC GATE OR 1CH 2-INP 5TSSOP"
